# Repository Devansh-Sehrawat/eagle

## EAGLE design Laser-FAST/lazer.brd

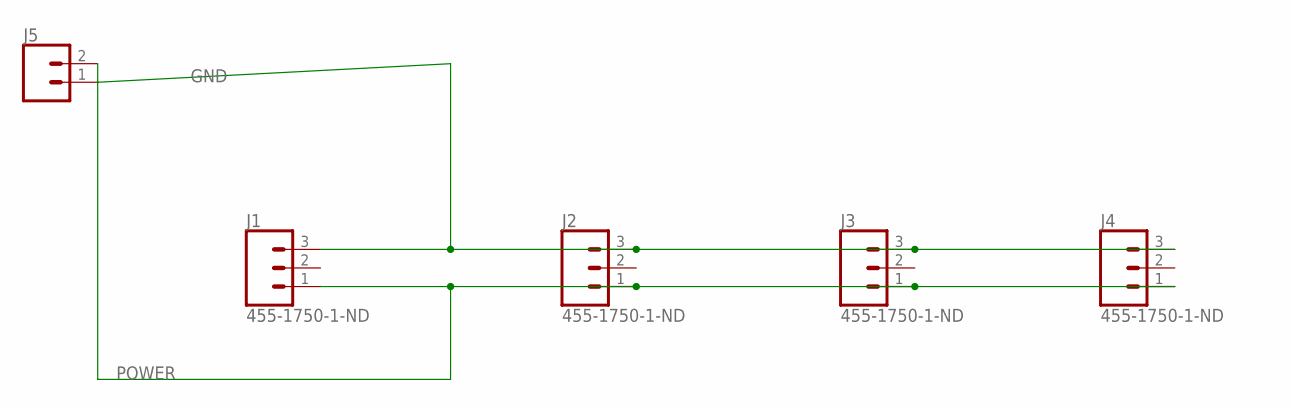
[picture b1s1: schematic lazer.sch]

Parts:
J1, J2, J3, J4: 455-1750-1-ND; 1X03
J5: CONN_02; 1X02

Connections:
GND: J1.3, J2.3, J3.3, J4.3, J5.1
POWER: J1.1, J2.1, J3.1, J4.1, J5.2

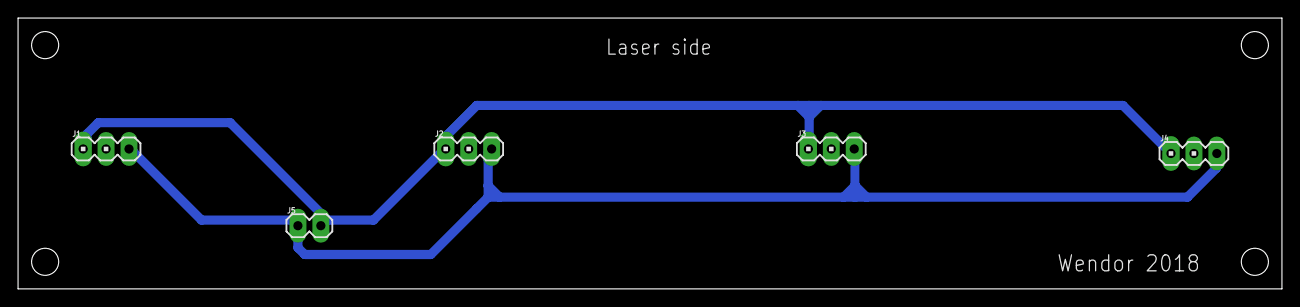
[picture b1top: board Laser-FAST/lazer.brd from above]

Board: 2 copper layers, 140.0 x 30.0 mm, 5 parts (0 on the bottom side), 2 nets.

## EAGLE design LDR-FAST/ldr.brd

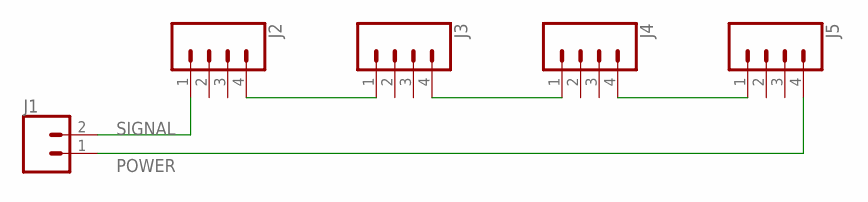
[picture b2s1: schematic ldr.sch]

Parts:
J1: CONN_02; 1X02
J2, J3, J4, J5: CONN_04; 1X04

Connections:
unnamed: J2.4, J3.1
unnamed: J3.4, J4.1
unnamed: J4.4, J5.1
POWER: J1.1, J5.4
SIGNAL: J1.2, J2.1

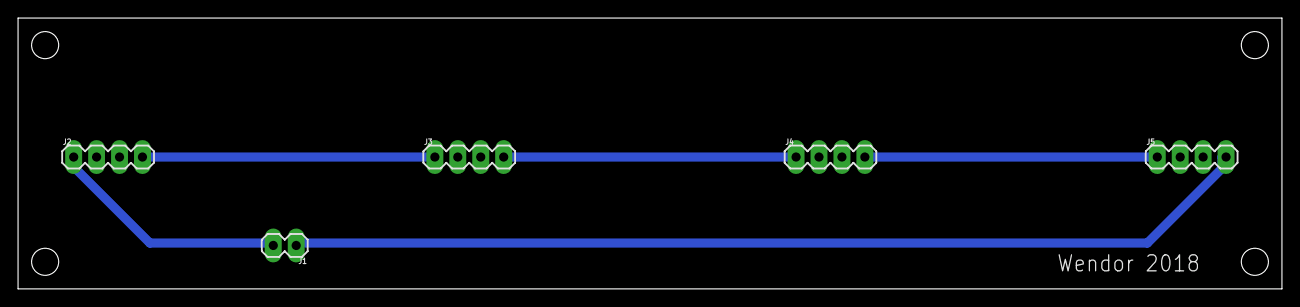
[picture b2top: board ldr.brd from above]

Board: 2 copper layers, 140.0 x 30.0 mm, 5 parts (0 on the bottom side), 5 nets.

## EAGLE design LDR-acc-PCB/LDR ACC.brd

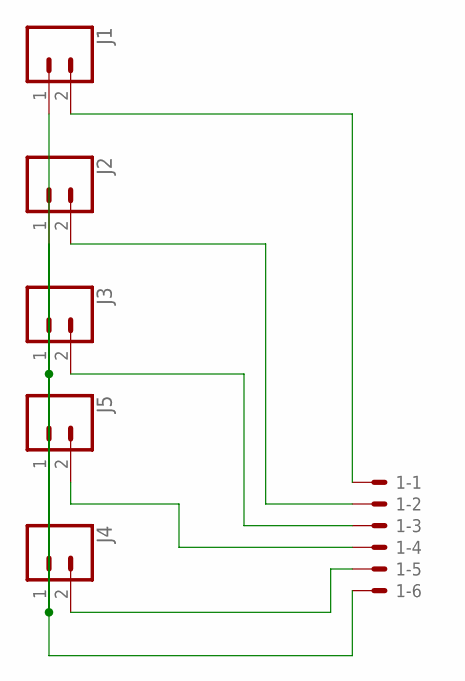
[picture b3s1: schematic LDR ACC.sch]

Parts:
1: 5566-6
J1, J2, J3, J4, J5: CONN_02PTH3; 1X02_LONGPADS

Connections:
unnamed: 1.6, J1.1, J2.1, J3.1, J4.1, J5.1
unnamed: 1.5, J4.2
unnamed: 1.4, J5.2
unnamed: 1.3, J3.2
unnamed: 1.2, J2.2
unnamed: 1.1, J1.2

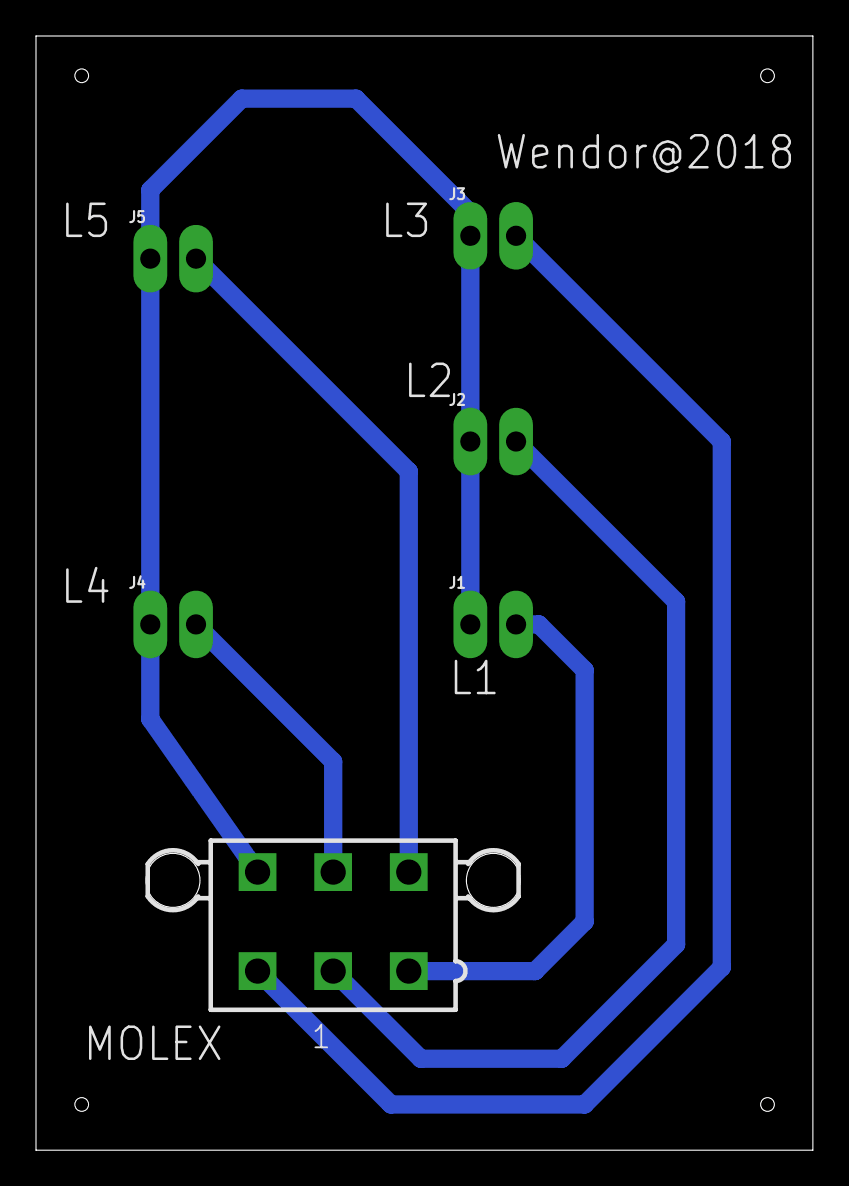
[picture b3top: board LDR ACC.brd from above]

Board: 2 copper layers, 43.2 x 61.9 mm, 6 parts (0 on the bottom side), 6 nets.

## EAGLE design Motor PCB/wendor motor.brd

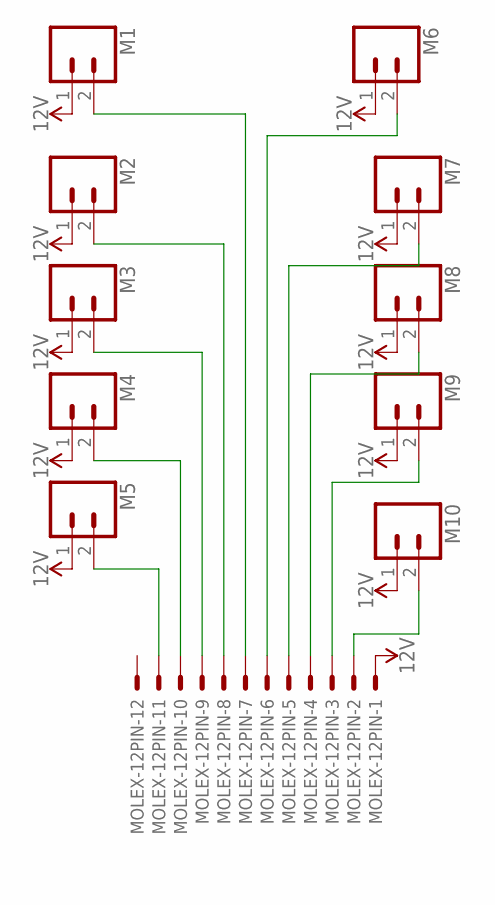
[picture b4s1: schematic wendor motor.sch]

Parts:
M1, M2, M3, M4, M5, M6, M7, M8, M9, M10: CONN_02; 1X02
MOLEX-12PIN: 5566-12

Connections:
12V: M1.1, M2.1, M3.1, M4.1, M5.1, M6.1, M7.1, M8.1, M9.1, M10.1, MOLEX-12PIN.1
unnamed: M5.2, MOLEX-12PIN.11
unnamed: M4.2, MOLEX-12PIN.10
unnamed: M3.2, MOLEX-12PIN.9
unnamed: M2.2, MOLEX-12PIN.8
unnamed: M1.2, MOLEX-12PIN.7
unnamed: M6.2, MOLEX-12PIN.6
unnamed: M7.2, MOLEX-12PIN.5
unnamed: M8.2, MOLEX-12PIN.4
unnamed: M9.2, MOLEX-12PIN.3
unnamed: M10.2, MOLEX-12PIN.2

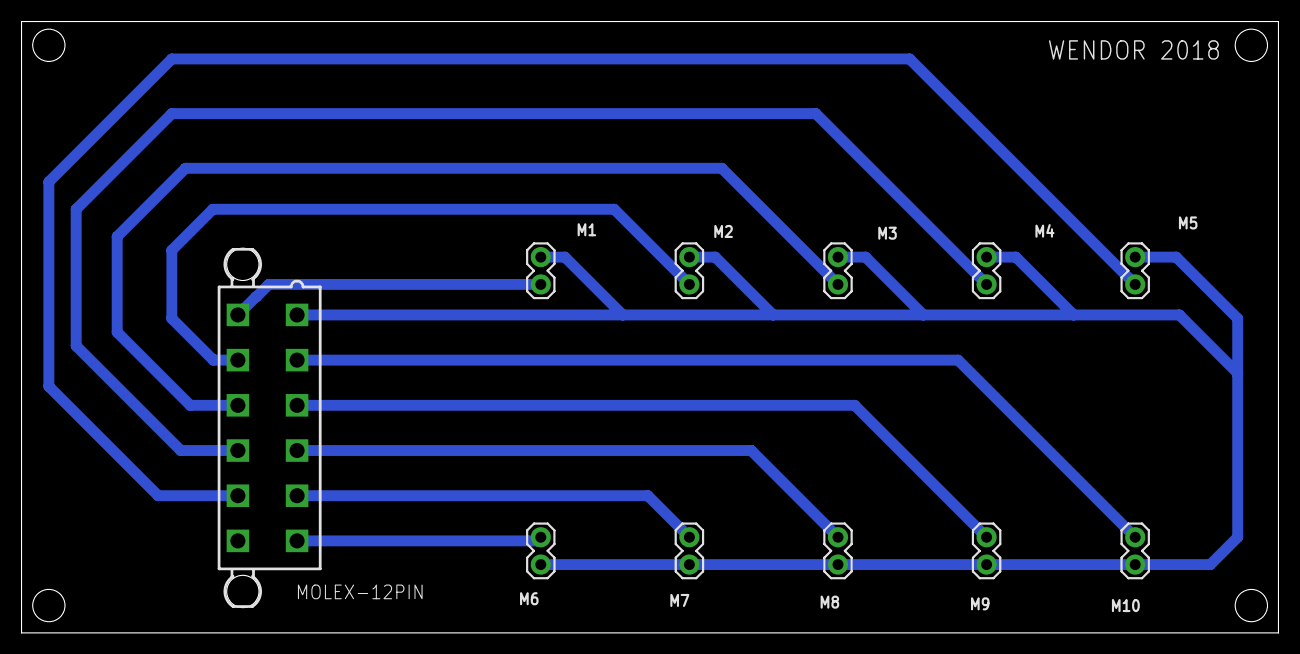
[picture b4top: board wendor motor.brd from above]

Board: 2 copper layers, 116.8 x 56.8 mm, 11 parts (0 on the bottom side), 11 nets.

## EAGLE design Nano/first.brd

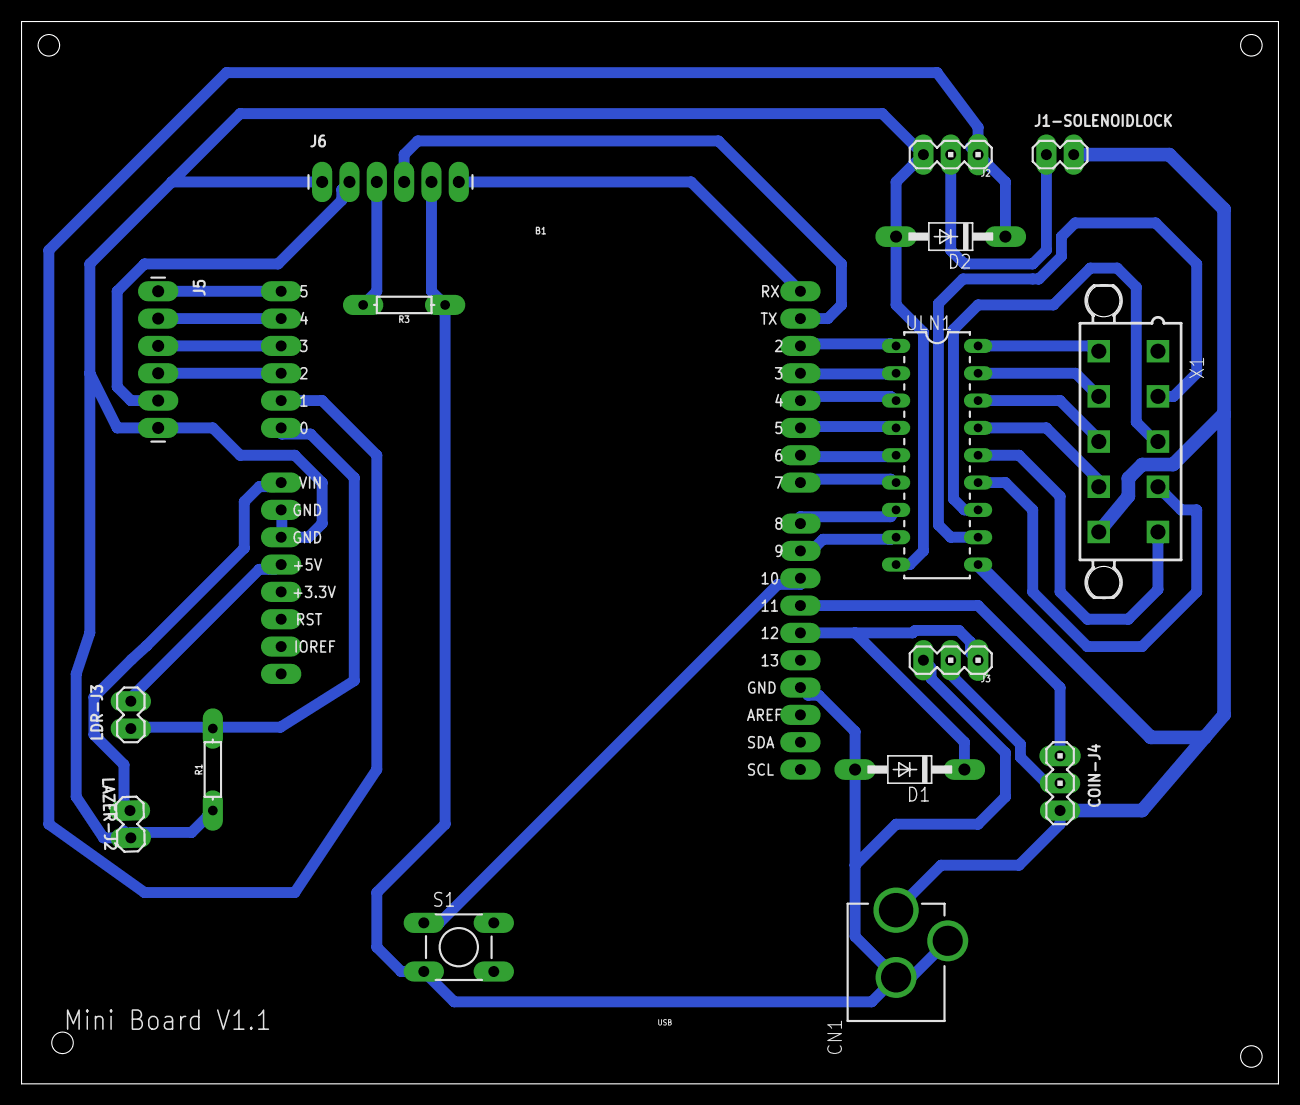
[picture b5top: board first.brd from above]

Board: 2 copper layers, 116.8 x 98.7 mm, 17 parts (0 on the bottom side), 35 nets.

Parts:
B1: ARDUINO_UNO_R3_SHIELDBASIC; UNO_R3_SHIELD
CN1: DCJACK_2MM_PTH
COIN-J4: 455-1750-1-ND; 1X03
D1, D2: 1N4004; DO41-10
J1-SOLENOIDLOCK: 1X02
J2, J3: 455-1750-1-ND; 1X03
J5, J6: 1X06_LONGPADS
LAZER-J2: 1X02
LDR-J3: 1X02
R1, R3: 1k; AXIAL-0.3
S1: TACTILE-PTH
ULN1: DIL18
X1: 5566-10

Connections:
+12V: CN1.PWR, COIN-J4.3, J1-SOLENOIDLOCK.2, ULN1.10, X1.10
GND: B1.GND@0, B1.GND@1, B1.GND@2, CN1.GND, CN1.GNDBREAK, D1.A, D2.A, J2.3, J3.3, J5.6, J6.1, J6.5, LAZER-J2.1, R1.P$1, R3.P$1, S1.3, ULN1.9
unnamed: B1.D2, ULN1.1
unnamed: B1.D3, ULN1.2
unnamed: B1.D4, ULN1.3
unnamed: B1.D5, ULN1.4
unnamed: B1.D6, ULN1.5
unnamed: B1.D7, ULN1.6
unnamed: B1.D8, ULN1.7
unnamed: B1.D9, ULN1.8
unnamed: ULN1.18, X1.6
unnamed: ULN1.17, X1.7
unnamed: ULN1.16, X1.8
unnamed: ULN1.15, X1.9
unnamed: ULN1.14, X1.5
unnamed: ULN1.13, X1.4
unnamed: ULN1.12, X1.3
unnamed: ULN1.11, X1.2
unnamed: B1.A0, LDR-J3.1, R1.P$2
unnamed: B1.VIN, LAZER-J2.2
unnamed: B1.D10, S1.1
unnamed: COIN-J4.2, J3.2
unnamed: B1.5V, LDR-J3.2
unnamed: B1.D11, COIN-J4.1
unnamed: B1.D12, D1.C, J3.1
unnamed: B1.A1, D2.C, J2.1
unnamed: J1-SOLENOIDLOCK.1, J2.2
unnamed: B1.TX, J6.4
unnamed: B1.RX, J6.6
unnamed: B1.A5, J5.1
unnamed: B1.A4, J5.2
unnamed: B1.A3, J5.3
unnamed: B1.A2, J5.4
unnamed: J5.5, J6.2
unnamed: J6.3, R3.P$2

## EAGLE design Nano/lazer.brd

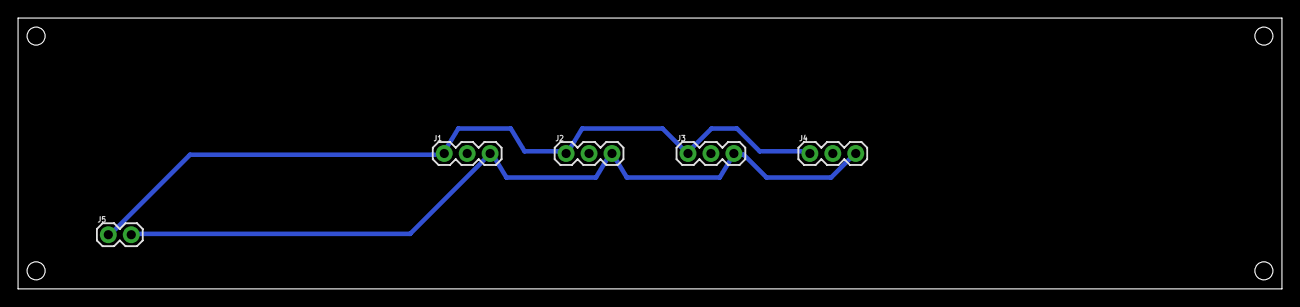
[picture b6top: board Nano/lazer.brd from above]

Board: 2 copper layers, 140.0 x 30.0 mm, 5 parts (0 on the bottom side), 2 nets.

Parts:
J1, J2, J3, J4: 1X03
J5: 1X02

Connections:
GND: J1.3, J2.3, J3.3, J4.3, J5.2
POWER: J1.1, J2.1, J3.1, J4.1, J5.1

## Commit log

2018-05-13 First commit \n1.Added molex connectors onto the big board\n2.Updated tracks width and vias
2018-05-13 Added small pcb with modifications
2018-05-14 Mini board schematic updated (molex conn added, uno mirrored, tracks and via changed)
2018-05-16 mini board(nano) and lazer-fast pcb modified(DRC errors)

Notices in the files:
parts and their libraries:
SparkFun-Connectors: Licensing: Creative Commons ShareAlike 4.0 International - https://creativecommons.org/licenses/by-sa/4.0
SparkFun: Licensing: CC v3.0 Share-Alike You are welcome to use this library for commercial purposes.
